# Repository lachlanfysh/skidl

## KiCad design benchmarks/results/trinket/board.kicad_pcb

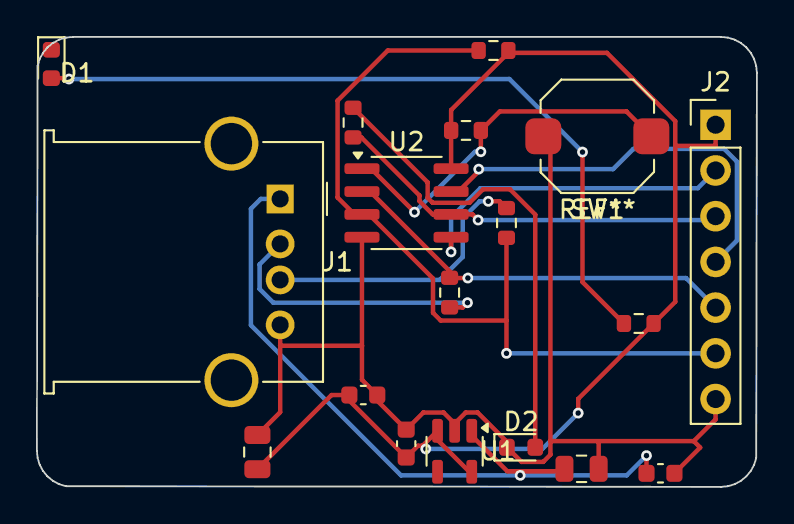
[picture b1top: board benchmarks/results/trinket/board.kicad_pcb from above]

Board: 2 copper layers, 40.0 x 25.0 mm, 18 parts (0 on the bottom side), 13 nets.

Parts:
C1, C3: 10uF; C_0805_2012Metric
C2, C4, C5: 100nF; C_0603_1608Metric
D1: GREEN; LED_0603_1608Metric
D2: RED; LED_0603_1608Metric
J1: USB_A; USB_A_Molex_67643_Horizontal
J2: GPIO; PinHeader_1x07_P2.54mm_Vertical
R1, R2: 68R; R_0603_1608Metric
R3: 1K5; R_0603_1608Metric
R4: 10K; R_0603_1608Metric
R5, R6: 1K; R_0603_1608Metric
SW1: RESET; SW_Push_1TS009xxxx-xxxx-xxxx_6x6x5mm
U1: MIC5205-3.3YM5; SOT-23-5
U2: ATtiny85; SOIC-8_3.9x4.9mm_P1.27mm

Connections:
3V3: C3.1, C4.1, C5.1, J2.1, R3.1, R4.1, R5.1, U1.3, U1.5, U2.8
GND: C1.2, C2.2, C3.2, C4.2, C5.2, D1.1, D2.1, J1.4, J2.7, SW1.2, U1.2, U2.4
unnamed: D1.2, R5.2
unnamed: D2.2, R6.2
PB0: J2.2, U2.5
PB1: J2.3, R6.1, U2.6
PB2: J2.4, U2.7
USB_DM: J2.5, R2.2, U2.2
USB_DM_RAW: J1.2, R2.1
USB_DP: J2.6, R1.2, R3.2, U2.3
USB_DP_RAW: J1.3, R1.1
VBUS: C1.1, C2.1, J1.1, U1.1
~RESET: R4.2, SW1.1, U2.1

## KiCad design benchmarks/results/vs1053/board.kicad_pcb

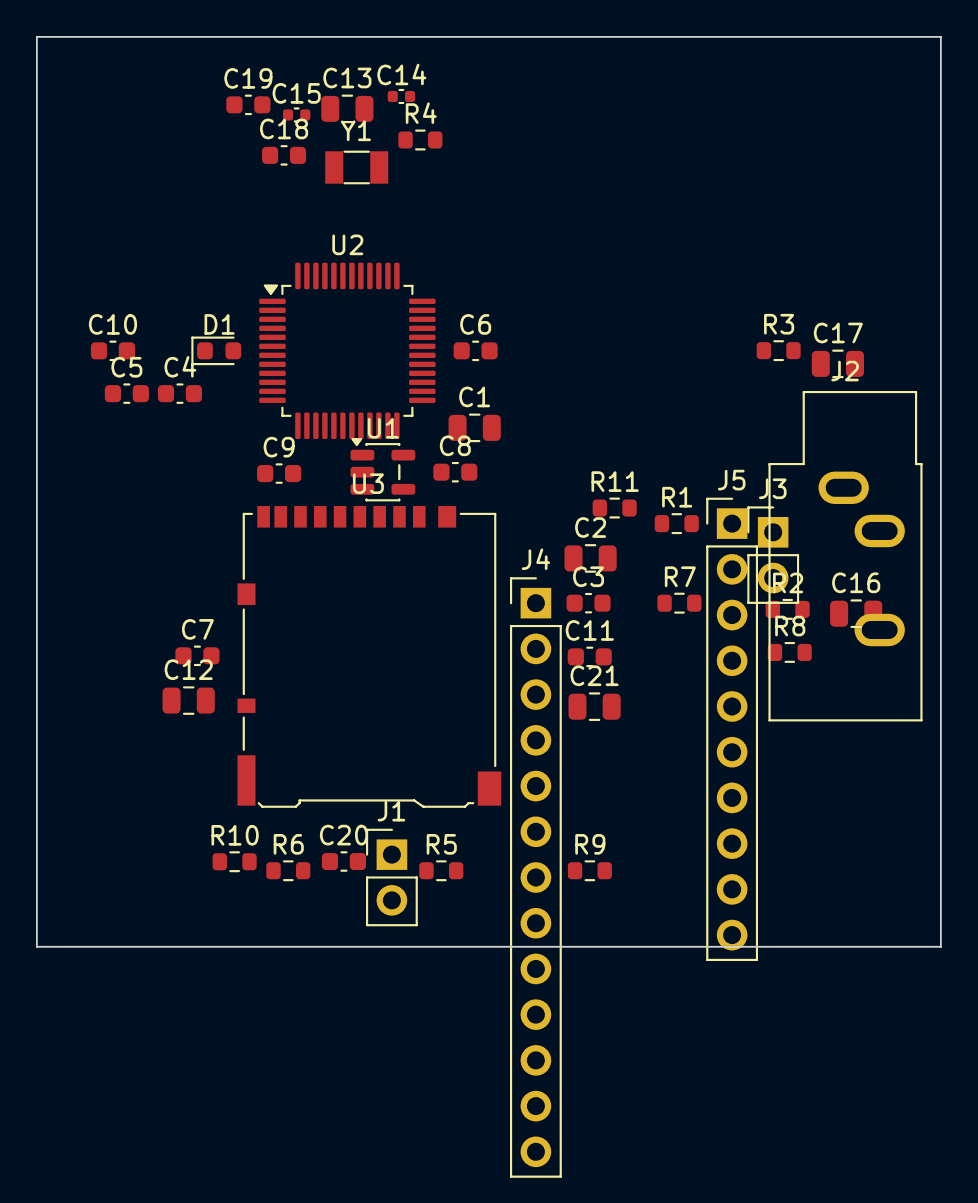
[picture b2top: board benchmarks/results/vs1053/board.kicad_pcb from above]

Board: 2 copper layers, 50.2 x 50.5 mm, 42 parts (0 on the bottom side), 38 nets, no tracks yet.

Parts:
C1, C2, C12, C13, C16, C17, C21: 10uF; C_0805_2012Metric
C3, C4, C5, C6, C7, C8, C9, C10, C11, C18, C19, C20: 100nF; C_0603_1608Metric
C14, C15: 15pF; C_0402_1005Metric
D1: GREEN; LED_0603_1608Metric
J1: PWR; PinHeader_1x02_P2.54mm_Vertical
J2: HP_JACK; Jack_3.5mm_CUI_SJ1-3533NG_Horizontal
J3: MIC; PinHeader_1x02_P2.54mm_Vertical
J4: SPI_HDR; PinHeader_1x13_P2.54mm_Vertical
J5: GPIO_HDR; PinHeader_1x10_P2.54mm_Vertical
R1: 1K; R_0603_1608Metric
R2, R3: 22; R_0603_1608Metric
R4: 2.2K; R_0603_1608Metric
R5, R6, R8, R9, R10: 10K; R_0603_1608Metric
R7: 100K; R_0603_1608Metric
R11: 220; R_0603_1608Metric
U1: AP2112K-3.3; SOT-23-5
U2: VS1053B; LQFP-48_7x7mm_P0.5mm
U3: MicroSD; microSD_HC_Hirose_DM3AT-SF-PEJM5
Y1: 12.288MHz; Crystal_SMD_3215-2Pin_3.2x1.5mm

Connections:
+1V8: C9.1, C10.1, C13.1, U2.5, U2.7, U2.21, U2.32, U2.42, U2.43
DREQ: J4.8, U2.8
GBUF: C5.1, U2.18
GND: C1.2, C2.2, C3.2, C4.2, C5.2, C6.2, C7.2, C8.2, C9.2, C10.2, C11.2, C12.2, C13.2, C14.2, C15.2, C19.2, C20.2, C21.2, J1.2, J2.S, J3.2, J4.2, J5.10, R1.2, U1.2, U2.15, U2.17, U2.31, U2.33, U2.38, U2.41, U2.44, U2.46, U3.6, U3.9
GPIO0: J5.1, U2.9
GPIO1: J5.2, U2.10
GPIO2: J5.3, U2.11
GPIO3: J5.4, U2.12
GPIO4: J5.5, U2.34
GPIO5: J5.6, U2.35
GPIO6: J5.7, U2.36
GPIO7: J5.8, U2.37
HP_L: C16.2, J2.T, R2.1
HP_R: C17.2, J2.R, R3.1
LINE_L: C16.1, U2.16
LINE_R: C17.1, U2.14
MIC_IN: C18.1, J3.1
MIC_N: C19.1, U2.2
MIC_P: C18.2, R4.2, U2.1
MIDI_RX: J5.9, R11.2, U2.23
MISO: J4.5, U2.27
MOSI: J4.4, U2.26
unnamed: D1.2, R1.1
unnamed: R5.2, U3.8
unnamed: R6.2, U3.1
RCAP: C4.1, U2.20
RESET_N: J4.9, R7.2, U2.30
SCI_CS: J4.6, R8.2, U2.28
SCK: J4.3, U2.25
SDI_CS: J4.7, R9.2, U2.40
SD_CS: J4.10, R10.2, U3.2
SD_MISO: J4.13, U3.7
SD_MOSI: J4.12, U3.3
SD_SCK: J4.11, U3.5
VCC: C2.1, C3.1, C6.1, C7.1, C8.1, C11.1, C12.1, C20.1, C21.1, D1.1, J4.1, R4.1, R5.1, R6.1, R7.1, R8.1, R9.1, R10.1, U1.5, U2.6, U2.13, U2.19, U2.22, U2.29, U2.39, U2.45, U3.4
VIN: C1.1, J1.1, U1.1, U1.3
XTAL_IN: C14.1, U2.3, Y1.1
XTAL_OUT: C15.1, U2.4, Y1.2

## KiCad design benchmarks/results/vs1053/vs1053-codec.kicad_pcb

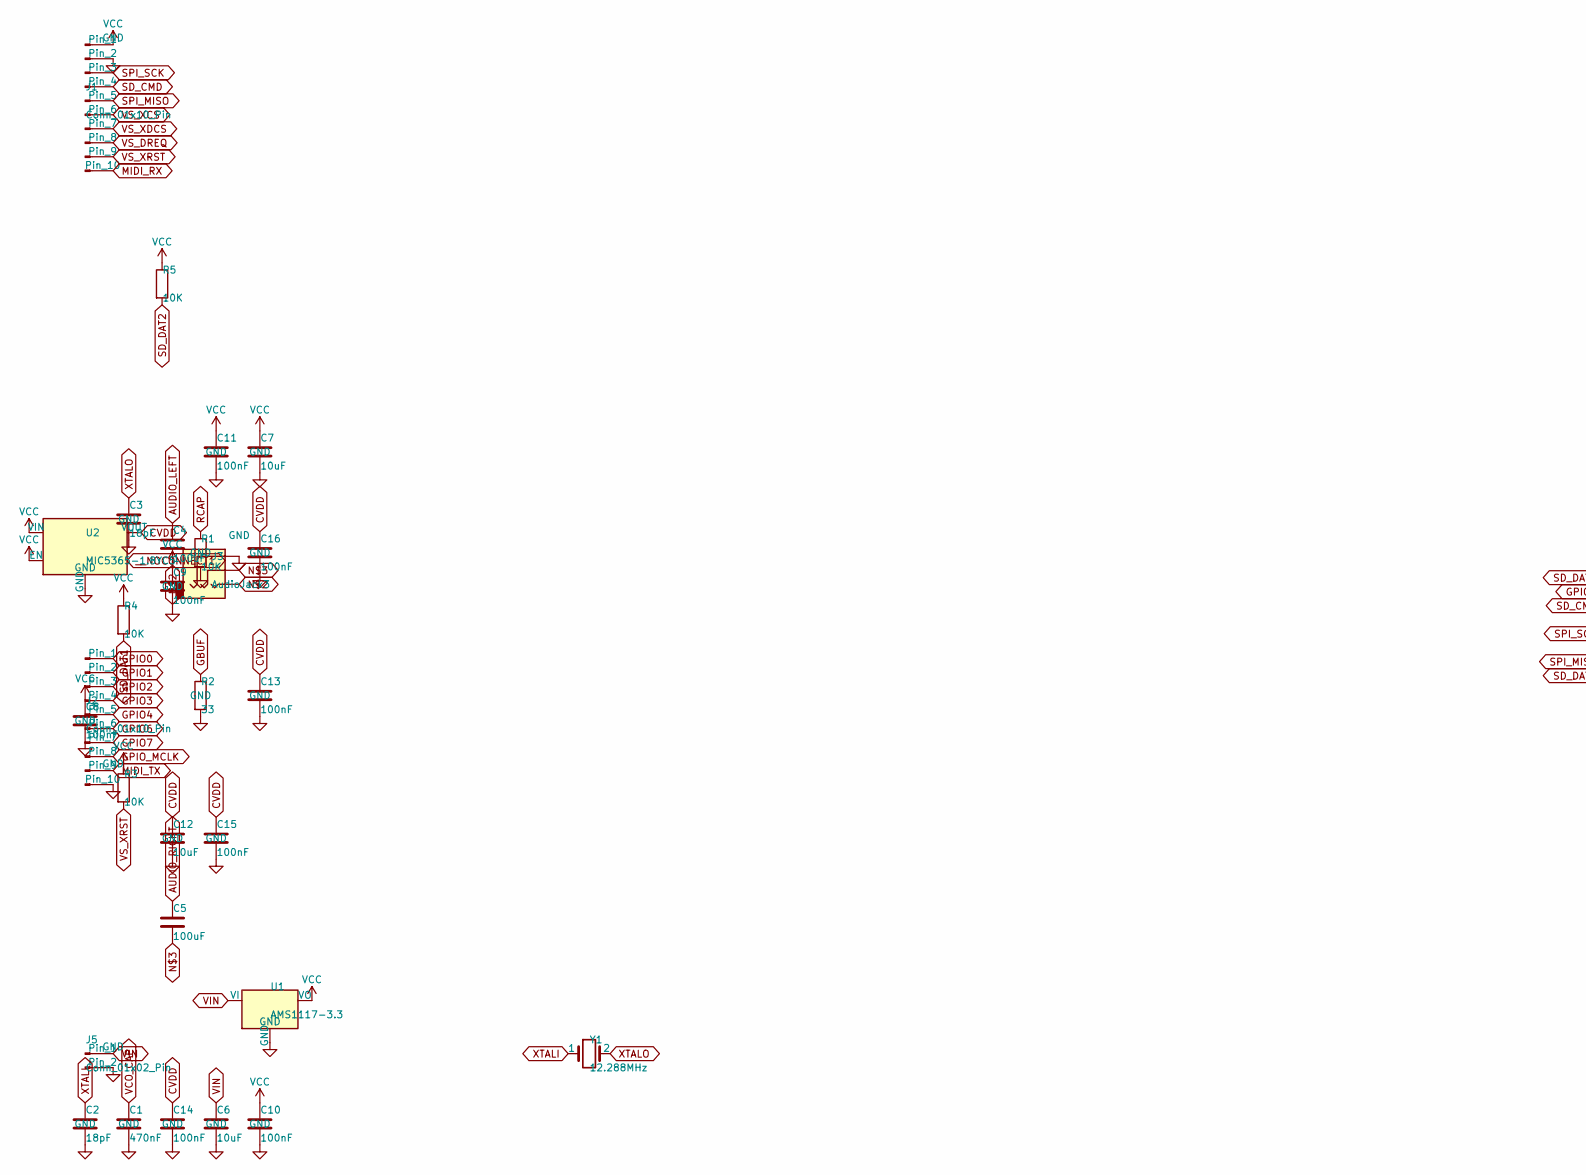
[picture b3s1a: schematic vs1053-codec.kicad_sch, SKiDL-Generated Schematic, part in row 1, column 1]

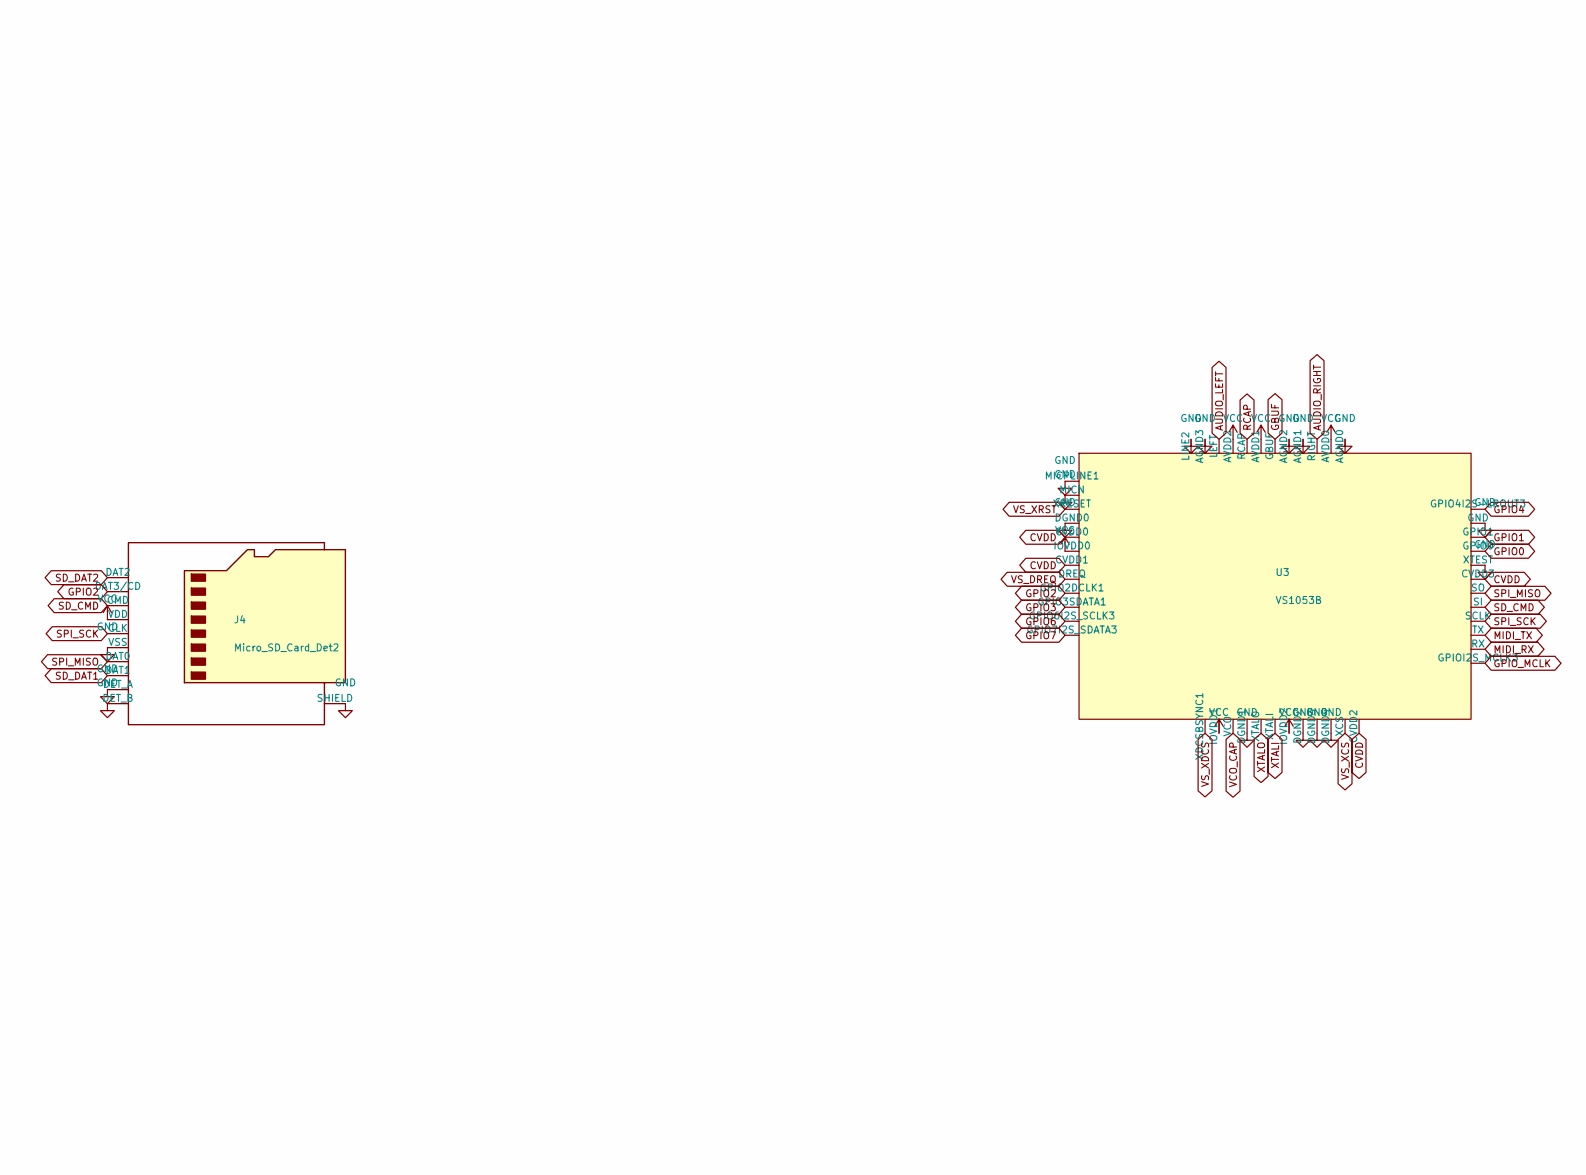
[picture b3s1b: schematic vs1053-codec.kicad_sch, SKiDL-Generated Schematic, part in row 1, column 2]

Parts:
C1: 470nF; C_0603_1608Metric
C2, C3: 18pF; C_0402_1005Metric
C4, C5: 100uF; C_1206_3216Metric
C6, C7, C12: 10uF; C_0805_2012Metric
C8, C9, C10, C11, C13, C14, C15, C16: 100nF; C_0603_1608Metric
J1, J2: Conn_01x10_Pin; PinHeader_1x10_P2.54mm_Vertical
J3: AudioJack3; Jack_3.5mm_CUI_SJ1-3513N_Horizontal
J4: Micro_SD_Card_Det2; microSD_HC_Hirose_DM3D-SF
J5: Conn_01x02_Pin; PinHeader_1x02_P2.54mm_Vertical
R1, R3, R4, R5: 10K; R_0603_1608Metric
R2: 33; R_0603_1608Metric
U1: AMS1117-3.3; SOT-223-3_TabPin2
U2: MIC5365-1.8YC5; SOT-353_SC-70-5
U3: VS1053B; LQFP-48_7x7mm_P0.5mm
Y1: 12.288MHz; Crystal_SMD_HC49-SD

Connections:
AUDIO_LEFT: C4.1, U3.46 (LEFT)
AUDIO_RIGHT: C5.1, U3.39 (RIGHT)
CVDD: C12.1, C13.1, C14.1, C15.1, C16.1, U2.5 (VOUT), U3.5 (CVDD0), U3.7 (CVDD1), U3.24 (CVDD2), U3.31 (CVDD3)
GBUF: R2.1, U3.42 (GBUF)
GND: C1.2, C2.2, C3.2, C6.2, C7.2, C8.2, C9.2, C10.2, C11.2, C12.2, C13.2, C14.2, C15.2, C16.2, J1.2, J2.10, J3.S, J4.6 (VSS), J4.9 (DET_B), J4.10 (DET_A), J4.11 (SHIELD), J5.2, R1.2, R2.2, U1.1 (GND), U2.2 (GND), U3.1 (MICPLINE1), U3.2 (MICN), U3.4 (DGND0), U3.16 (DGND1), U3.20 (DGND2), U3.21 (DGND3), U3.22 (DGND4), U3.32 (XTEST), U3.35 (GND), U3.37 (AGND0), U3.40 (AGND1), U3.41 (AGND2), U3.47 (AGND3), U3.48 (LINE2)
GPIO0: J2.1, U3.33 (GPIO0)
GPIO1: J2.2, U3.34 (GPIO1)
GPIO2: J2.3, J4.2 (DAT3/CD), U3.9 (GPIO2DCLK1)
GPIO3: J2.4, U3.10 (GPIO3SDATA1)
GPIO4: J2.5, U3.36 (GPIO4I2S-LROUT3)
GPIO6: J2.6, U3.11 (GPIO6I2S_SCLK3)
GPIO7: J2.7, U3.12 (GPIO7I2S_SDATA3)
GPIO_MCLK: J2.8, U3.25 (GPIOI2S_MCLK3)
MIDI_RX: J1.10, U3.26 (RX)
MIDI_TX: J2.9, U3.27 (TX)
unnamed: C5.2, J3.R
RCAP: R1.1, U3.44 (RCAP)
SD_CMD: J1.4, J4.3 (CMD), U3.29 (SI)
SD_DAT1: J4.8 (DAT1), R4.2
SD_DAT2: J4.1 (DAT2), R5.2
SPI_MISO: J1.5, J4.7 (DAT0), U3.30 (SO)
SPI_SCK: J1.3, J4.5 (CLK), U3.28 (SCLK)
VCO_CAP: C1.1, U3.15 (VCO)
VIN: C6.1, J5.1, U1.3 (VI)
VS_DREQ: J1.8, U3.8 (DREQ)
VS_XCS: J1.6, U3.23 (XCS)
VS_XDCS: J1.7, U3.13 (XDCSBSYNC1)
VS_XRST: J1.9, R3.2, U3.3 (XRESET)
XTALI: C2.1, U3.18 (XTALI), Y1.1
XTALO: C3.1, U3.17 (XTALO), Y1.2
__NOCONNECT1: U2.4 (NC)

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
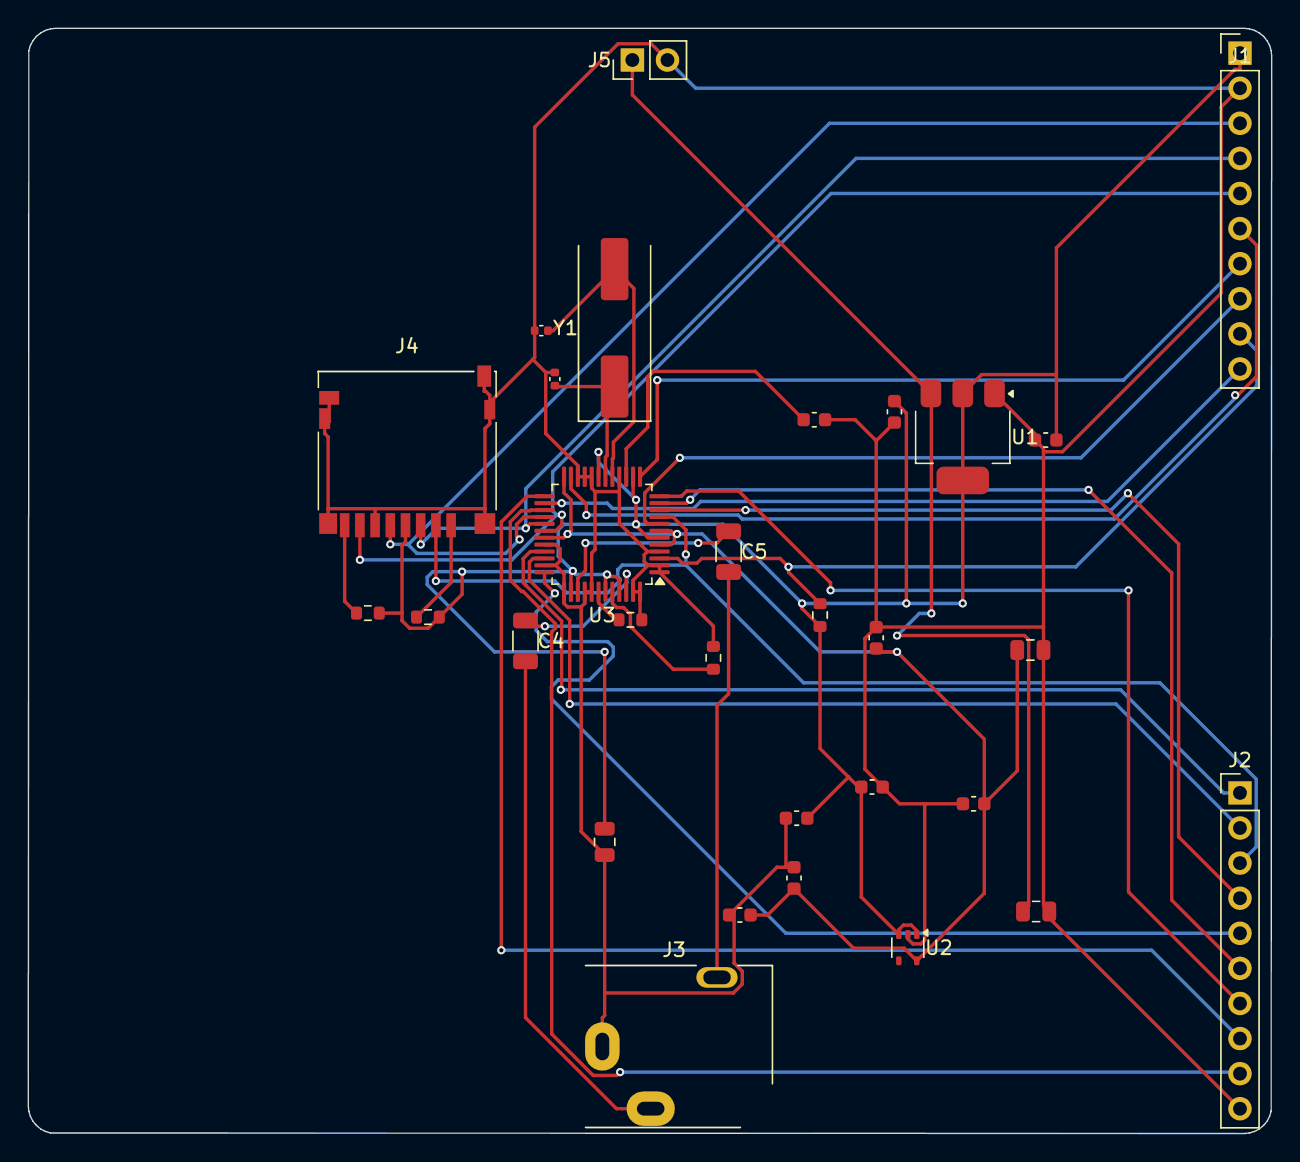
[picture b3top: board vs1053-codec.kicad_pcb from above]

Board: 2 copper layers, 90.0 x 80.0 mm, 30 parts (0 on the bottom side), 32 nets.

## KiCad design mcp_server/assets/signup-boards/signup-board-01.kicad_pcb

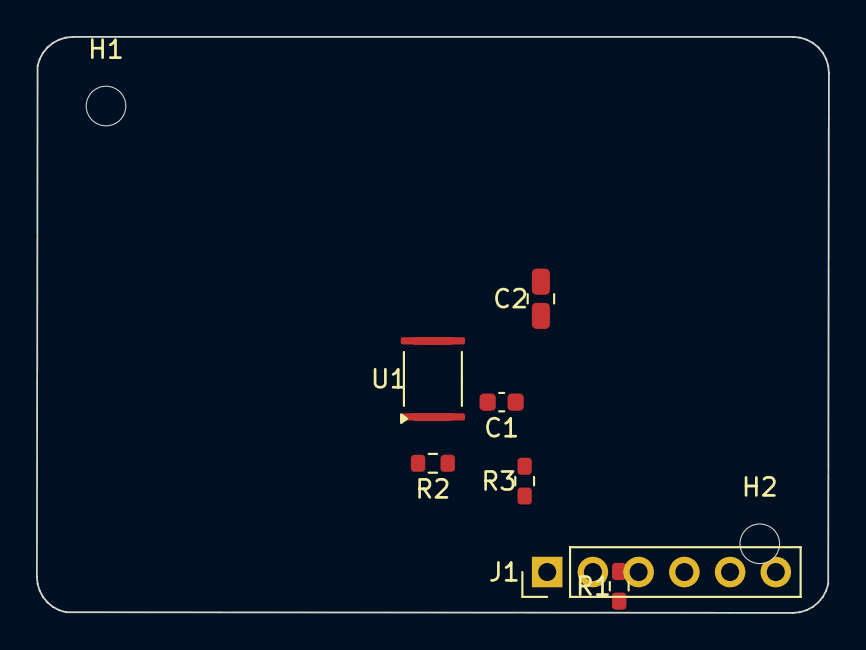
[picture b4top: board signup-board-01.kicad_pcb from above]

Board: 2 copper layers, 44.0 x 32.0 mm, 9 parts (0 on the bottom side), 5 nets, no tracks yet.

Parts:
C1: 100nF; C_0603_1608Metric
C2: 10uF; C_0805_2012Metric
H1, H2: MountingHole; MountingHole_2.2mm_M2
J1: Conn_01x06; PinHeader_1x06_P2.54mm_Vertical
R1, R2, R3: 10K; R_0603_1608Metric
U1: MCP9808_MSOP; MSOP-8_3x3mm_P0.65mm

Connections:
GND: C1.2, C2.2, J1.2, U1.4, U1.5, U1.6, U1.7
unnamed: J1.5, R3.2, U1.3
SCL: J1.4, R2.2, U1.2
SDA: J1.3, R1.2, U1.1
VDD: C1.1, C2.1, J1.1, R1.1, R2.1, R3.1, U1.8

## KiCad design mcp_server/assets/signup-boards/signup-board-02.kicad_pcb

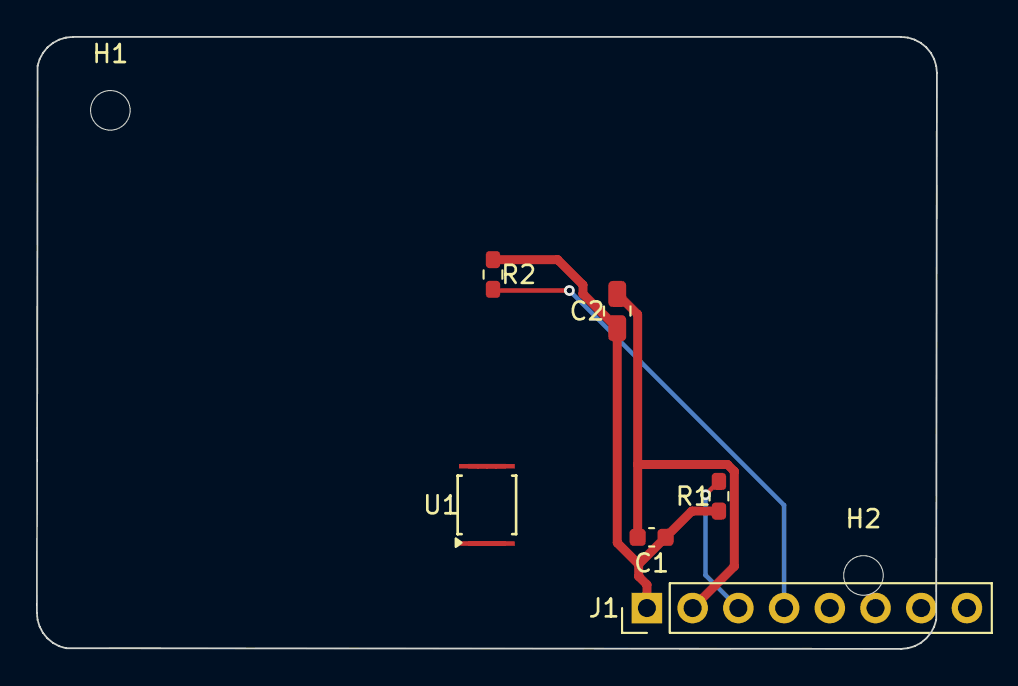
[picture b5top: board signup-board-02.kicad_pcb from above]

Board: 2 copper layers, 50.0 x 34.0 mm, 8 parts (0 on the bottom side), 8 nets.

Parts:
C1: 100nF; C_0603_1608Metric
C2: 10uF; C_0805_2012Metric
H1, H2: MountingHole; MountingHole_2.2mm_M2
J1: Conn_01x08; PinHeader_1x08_P2.54mm_Vertical
R1, R2: 10K; R_0603_1608Metric
U1: ADS1115IDGS; TSSOP-10_3x3mm_P0.5mm

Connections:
GND: C1.2, C2.2, J1.2, U1.1, U1.3
unnamed: J1.5, U1.4
unnamed: J1.6, U1.5
unnamed: J1.7, U1.6
unnamed: J1.8, U1.7
SCL: J1.4, R2.2, U1.10
SDA: J1.3, R1.2, U1.9
VDD: C1.1, C2.1, J1.1, R1.1, R2.1, U1.8

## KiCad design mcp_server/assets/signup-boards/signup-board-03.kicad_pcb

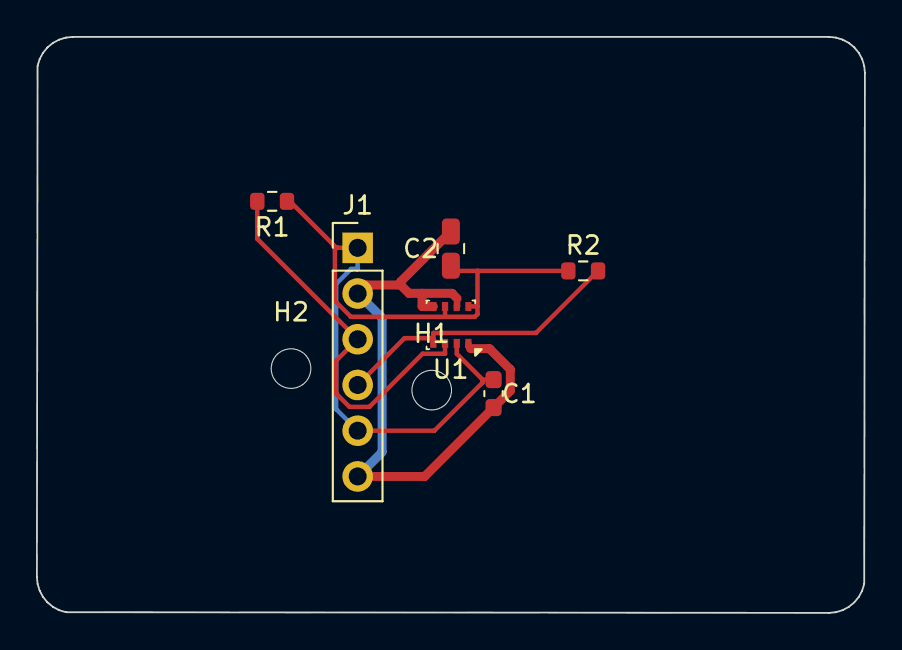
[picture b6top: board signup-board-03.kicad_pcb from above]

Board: 2 copper layers, 46.0 x 32.0 mm, 8 parts (0 on the bottom side), 4 nets.

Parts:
C1: 100nF; C_0603_1608Metric
C2: 10uF; C_0805_2012Metric
H1, H2: MountingHole; MountingHole_2.2mm_M2
J1: Conn_01x06; PinHeader_1x06_P2.54mm_Vertical
R1, R2: 10K; R_0603_1608Metric
U1: BME280; Bosch_LGA-8_2.5x2.5mm_P0.65mm_ClockwisePinNumbering

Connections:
3V3: C1.1, C2.1, J1.1, J1.5, R1.1, R2.1, U1.2, U1.6, U1.8
GND: C1.2, C2.2, J1.2, J1.6, U1.1, U1.5, U1.7
SCL: J1.4, R2.2, U1.4
SDA: J1.3, R1.2, U1.3

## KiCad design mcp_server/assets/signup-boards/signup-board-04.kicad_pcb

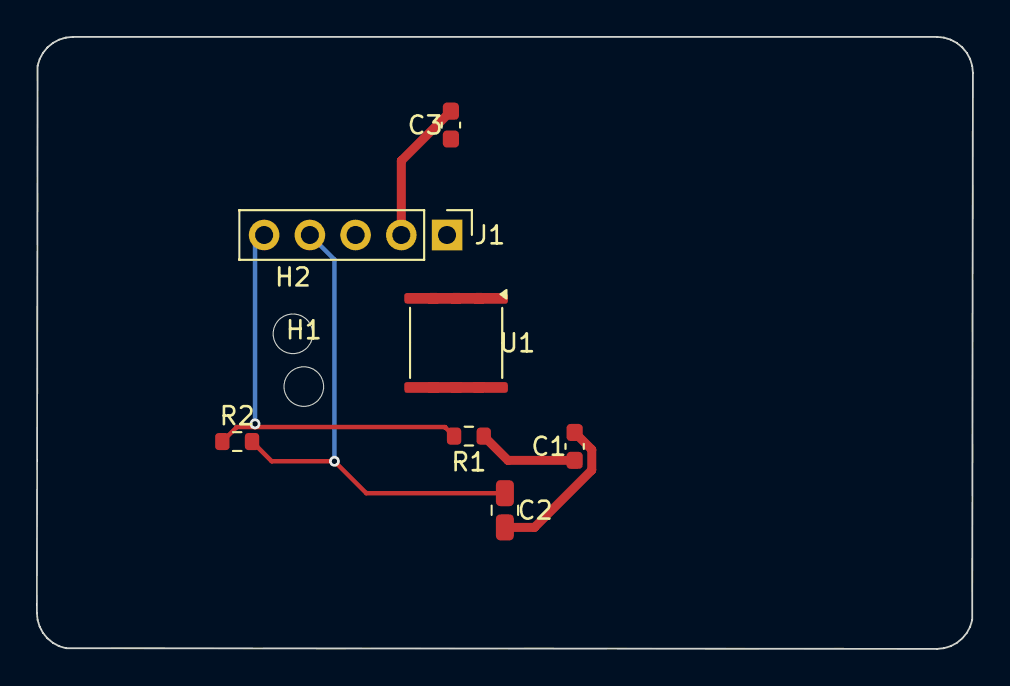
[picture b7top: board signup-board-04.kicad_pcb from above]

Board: 2 copper layers, 52.0 x 34.0 mm, 9 parts (0 on the bottom side), 6 nets.

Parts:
C1: 100nF; C_0603_1608Metric
C2: 10uF; C_0805_2012Metric
C3: 10nF; C_0603_1608Metric
H1, H2: MountingHole; MountingHole_2.2mm_M2
J1: Conn_01x05; PinHeader_1x05_P2.54mm_Vertical
R1: 10K; R_0603_1608Metric
R2: 100K; R_0603_1608Metric
U1: NE555D; SOIC-8_3.9x4.9mm_P1.27mm

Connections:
DISCH: J1.5, R1.2, R2.1, U1.7
GND: C1.2, C2.2, C3.2, J1.2, U1.1
unnamed: C3.1, U1.5
OUT: J1.3, U1.3
THRESH: C2.1, J1.4, R2.2, U1.2, U1.6
VCC: C1.1, J1.1, R1.1, U1.4, U1.8

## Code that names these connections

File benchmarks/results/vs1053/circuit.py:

from skidl import *

# Power rails
vin = Net("VIN"); vin.drive = POWER        # 5V input
vcc3v3 = Net("VCC"); vcc3v3.drive = POWER  # 3.3V digital/IO/analog rail
vcc1v8 = Net("CVDD"); vcc1v8.drive = POWER # 1.8V core rail for VS1053
gnd = Net("GND"); gnd.drive = POWER

# 3.3V LDO (AMS1117-3.3, SOT-223, 1A)
u_3v3 = Part("Regulator_Linear", "AMS1117-3.3",
             footprint="Package_TO_SOT_SMD:SOT-223-3_TabPin2")
vin += u_3v3["VI"]
gnd += u_3v3["GND"]
vcc3v3 += u_3v3["VO"]

# 1.8V LDO for VS1053 core (MIC5365-1.8YC5, SOT-353, 150mA)
u_1v8 = Part("Regulator_Linear", "MIC5365-1.8YC5",
             footprint="Package_TO_SOT_SMD:SOT-353_SC-70-5")
vcc3v3 += u_1v8["VIN"]
vcc3v3 += u_1v8["EN"]   # EN tied high = always on
gnd += u_1v8["GND"]
vcc1v8 += u_1v8["VOUT"]
u_1v8["NC"] += NC()

# VS1053B audio codec (EasyEDA/LCSC C9922, LQFP-48)
vs = Part("C9922", "VS1053B",
          footprint="Package_QFP:LQFP-48_7x7mm_P0.5mm")

# Core power (1.8V) — pins 5,7,24,31
vcc1v8 += vs["CVDD0"], vs["CVDD1"], vs["CVDD2"], vs["CVDD3"]
# IO power (3.3V) — pins 6,14,19
vcc3v3 += vs["IOVDD0"], vs["IOVDD1"], vs["IOVDD2"]
# Analog power (3.3V) — pins 38,43,45
vcc3v3 += vs["AVDD0"], vs["AVDD1"], vs["AVDD2"]
# Digital ground — pins 4,16,20,21,22,35
gnd += vs["DGND0"], vs["DGND1"], vs["DGND2"], vs["DGND3"], vs["DGND4"], vs["GND"]
# Analog ground — pins 37,40,41,47
gnd += vs["AGND0"], vs["AGND1"], vs["AGND2"], vs["AGND3"]

# XTEST: pull to GND for normal operation (pin 32)
gnd += vs["XTEST"]

# VCO filter cap (pin 15)
vco_net = Net("VCO_CAP")
vs["VCO"] += vco_net
c_vco = Part("Device", "C", value="470nF",
             footprint="Capacitor_SMD:C_0603_1608Metric")
vco_net += c_vco[1]
gnd += c_vco[2]

# RCAP: output resistance cap (pin 44) — 10K to GND
rcap_net = Net("RCAP")
vs["RCAP"] += rcap_net
r_rcap = Part("Device", "R", value="10K",
              footprint="Resistor_SMD:R_0603_1608Metric")
rcap_net += r_rcap[1]
gnd += r_rcap[2]

# GBUF: buffer output (pin 42) — 33 ohm to GND
gbuf_net = Net("GBUF")
vs["GBUF"] += gbuf_net
r_gbuf = Part("Device", "R", value="33",
              footprint="Resistor_SMD:R_0603_1608Metric")
gbuf_net += r_gbuf[1]
gnd += r_gbuf[2]

# 12.288 MHz crystal (pins 17=XTALO, 18=XTALI)
xtal = Part("Device", "Crystal",
            footprint="Crystal:Crystal_SMD_HC49-SD")
xtal.value = "12.288MHz"

xtali_net = Net("XTALI")
xtalo_net = Net("XTALO")
vs["XTALI"] += xtali_net
vs["XTALO"] += xtalo_net
xtal[1] += xtali_net
xtal[2] += xtalo_net

# Crystal load caps (18pF)
c_xi = Part("Device", "C", value="18pF",
            footprint="Capacitor_SMD:C_0402_1005Metric")
c_xo = Part("Device", "C", value="18pF",
            footprint="Capacitor_SMD:C_0402_1005Metric")
xtali_net += c_xi[1]; gnd += c_xi[2]
xtalo_net += c_xo[1]; gnd += c_xo[2]

# SPI interface signals
spi_sck  = Net("SPI_SCK")
spi_mosi = Net("SPI_MOSI")
spi_miso = Net("SPI_MISO")
vs_xcs   = Net("VS_XCS")    # VS1053 SPI control chip select (pin 23)
vs_xdcs  = Net("VS_XDCS")   # VS1053 SPI data chip select / BSYNC (pin 13)
vs_dreq  = Net("VS_DREQ")   # data request output (pin 8)
vs_xrst  = Net("VS_XRST")   # reset active-low (pin 3)
midi_rx  = Net("MIDI_RX")   # UART RX for MIDI (pin 26)
midi_tx  = Net("MIDI_TX")   # UART TX (pin 27)

vs["SCLK"] += spi_sck
vs["SI"]   += spi_mosi
vs["SO"]   += spi_miso
vs["XCS"]  += vs_xcs
vs["XDCSBSYNC1"] += vs_xdcs
vs["DREQ"] += vs_dreq
vs["XRESET"] += vs_xrst
vs["RX"]   += midi_rx
vs["TX"]   += midi_tx

# XRESET pull-up resistor
r_xrst = Part("Device", "R", value="10K",
              footprint="Resistor_SMD:R_0603_1608Metric")
vcc3v3 += r_xrst[1]
vs_xrst += r_xrst[2]

# GPIO signals (pins 33,34,9,10,36,11,12,25)
gpio0     = Net("GPIO0")
gpio1     = Net("GPIO1")
gpio2     = Net("GPIO2")
gpio3     = Net("GPIO3")
gpio4     = Net("GPIO4")
gpio6     = Net("GPIO6")
gpio7     = Net("GPIO7")
gpio_mclk = Net("GPIO_MCLK")

vs["GPIO0"]          += gpio0
vs["GPIO1"]          += gpio1
vs["GPIO2DCLK1"]     += gpio2
vs["GPIO3SDATA1"]    += gpio3
vs["GPIO4I2S-LROUT3"]  += gpio4
vs["GPIO6I2S_SCLK3"]   += gpio6
vs["GPIO7I2S_SDATA3"]  += gpio7
vs["GPIOI2S_MCLK3"]    += gpio_mclk

# MIC input pins — tie MICPLINE1 and LINE2 to AGND for breakout
gnd += vs["MICPLINE1"], vs["MICN"], vs["LINE2"]

# SPI header — 10 pin (3V3, GND, SCK, MOSI, MISO, XCS, XDCS, DREQ, XRST, MIDI_RX)
j_spi = Part("Connector", "Conn_01x10_Pin",
             footprint="Connector_PinHeader_2.54mm:PinHeader_1x10_P2.54mm_Vertical")
j_spi.edge_preference = "right"
vcc3v3  += j_spi["Pin_1"]
gnd     += j_spi["Pin_2"]
spi_sck  += j_spi["Pin_3"]
spi_mosi += j_spi["Pin_4"]
spi_miso += j_spi["Pin_5"]
vs_xcs   += j_spi["Pin_6"]
vs_xdcs  += j_spi["Pin_7"]
vs_dreq  += j_spi["Pin_8"]
vs_xrst  += j_spi["Pin_9"]
midi_rx  += j_spi["Pin_10"]

# GPIO header — 10 pin (GPIO0..7, MIDI_TX, GND)
j_gpio = Part("Connector", "Conn_01x10_Pin",
              footprint="Connector_PinHeader_2.54mm:PinHeader_1x10_P2.54mm_Vertical")
j_gpio.edge_preference = "right"
gpio0     += j_gpio["Pin_1"]
gpio1     += j_gpio["Pin_2"]
gpio2     += j_gpio["Pin_3"]
gpio3     += j_gpio["Pin_4"]
gpio4     += j_gpio["Pin_5"]
gpio6     += j_gpio["Pin_6"]
gpio7     += j_gpio["Pin_7"]
gpio_mclk += j_gpio["Pin_8"]
midi_tx  += j_gpio["Pin_9"]
gnd      += j_gpio["Pin_10"]

# 3.5mm stereo headphone jack
# CUI SJ1-3513N footprint uses pad names T/R/S — matches AudioJack3 symbol pin numbers
j_hp = Part("Connector_Audio", "AudioJack3",
            footprint="Connector_Audio:Jack_3.5mm_CUI_SJ1-3513N_Horizontal")
j_hp.edge_preference = "bottom"

# Line output coupling caps (100uF — SMD 1206)
audio_left_raw  = Net("AUDIO_LEFT")
audio_right_raw = Net("AUDIO_RIGHT")
vs["LEFT"]  += audio_left_raw
vs["RIGHT"] += audio_right_raw

c_left = Part("Device", "C", value="100uF",
              footprint="Capacitor_SMD:C_1206_3216Metric")
c_right = Part("Device", "C", value="100uF",
               footprint="Capacitor_SMD:C_1206_3216Metric")
audio_left_raw  += c_left[1];  c_left[2]  += j_hp["T"]   # Tip = Left
audio_right_raw += c_right[1]; c_right[2] += j_hp["R"]   # Ring = Right
gnd += j_hp["S"]                                           # Sleeve = GND

# MicroSD socket (SPI mode) — Hirose DM3D-SF has 11 pads; use Micro_SD_Card_Det2 (11 pins)
sd = Part("Connector", "Micro_SD_Card_Det2",
          footprint="Connector_Card:microSD_HC_Hirose_DM3D-SF")

sd_clk  = Net("SD_CLK")
sd_cmd  = Net("SD_CMD")   # MOSI in SPI mode
sd_dat0 = Net("SD_DAT0")  # MISO in SPI mode
sd_cs   = Net("SD_CS")    # CS (DAT3/CD in SPI mode)
sd_dat1 = Net("SD_DAT1")
sd_dat2 = Net("SD_DAT2")

vcc3v3 += sd["VDD"]
gnd    += sd["VSS"]
gnd    += sd["SHIELD"]
# Card detect pins: DET_A and DET_B are normally-closed switch; tie both to GND
gnd    += sd["DET_A"]
gnd    += sd["DET_B"]

# SD shares the SPI bus with VS1053
spi_sck  += sd_clk;  sd["CLK"]     += sd_clk
spi_mosi += sd_cmd;  sd["CMD"]     += sd_cmd
spi_miso += sd_dat0; sd["DAT0"]    += sd_dat0
sd_cs    += sd["DAT3/CD"]

# SD unused data lines pulled high
sd["DAT1"] += sd_dat1
sd["DAT2"] += sd_dat2
r_sd1 = Part("Device", "R", value="10K", footprint="Resistor_SMD:R_0603_1608Metric")
r_sd2 = Part("Device", "R", value="10K", footprint="Resistor_SMD:R_0603_1608Metric")
vcc3v3 += r_sd1[1]; sd_dat1 += r_sd1[2]
vcc3v3 += r_sd2[1]; sd_dat2 += r_sd2[2]

# SD CS on its own GPIO2 line (or bring out on separate header pin)
gpio2 += sd_cs

# 5V input power connector
j_pwr = Part("Connector", "Conn_01x02_Pin",
             footprint="Connector_PinHeader_2.54mm:PinHeader_1x02_P2.54mm_Vertical")
j_pwr.edge_preference = "top"
vin += j_pwr["Pin_1"]
gnd += j_pwr["Pin_2"]

# --- Decoupling caps ---

# VIN 10uF bulk
c_vin = Part("Device", "C", value="10uF", footprint="Capacitor_SMD:C_0805_2012Metric")
vin += c_vin[1]; gnd += c_vin[2]

# 3.3V rail: 10uF bulk + 100nF x4
c_3v3_b = Part("Device", "C", value="10uF", footprint="Capacitor_SMD:C_0805_2012Metric")
vcc3v3 += c_3v3_b[1]; gnd += c_3v3_b[2]
for _ in range(4):
    c = Part("Device", "C", value="100nF", footprint="Capacitor_SMD:C_0603_1608Metric")
    vcc3v3 += c[1]; gnd += c[2]

# 1.8V CVDD rail: 10uF bulk + 100nF x4
c_1v8_b = Part("Device", "C", value="10uF", footprint="Capacitor_SMD:C_0805_2012Metric")
vcc1v8 += c_1v8_b[1]; gnd += c_1v8_b[2]
for _ in range(4):
    c = Part("Device", "C", value="100nF", footprint="Capacitor_SMD:C_0603_1608Metric")
    vcc1v8 += c[1]; gnd += c[2]

# Larger board outline to reduce congestion on dense LQFP-48
EDA_FLOORPLAN = {
    "outline": {"width_mm": 90, "height_mm": 80, "corner_radius_mm": 2},
    "edge_anchors": [
        {"ref": "J3", "edge": "bottom"},
        {"ref": "J5", "edge": "top"},
    ],
}

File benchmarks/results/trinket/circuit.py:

"""
Trinket ATtiny85 dev board — SKiDL circuit description.

Based on the Adafruit Trinket hardware:
- ATtiny85-20S (SOIC-8) MCU with V-USB software USB
- USB-A male plug (horizontal, plugs directly into host USB port)
- MIC5225-3.3YM5 SOT-23-5 3.3V LDO regulator
- Green power LED (always on)
- Red user LED on PB1 (Arduino digital pin 1)
- Tactile reset button
- 5 GPIO pins broken out on 0.1" header
- Board ~31x15mm

V-USB wiring (low-speed, per Adafruit Trinket reference design):
  D- → PB3/XTAL1 (pin 2) via 68R
  D+ → PB4/XTAL2 (pin 3) via 68R + 1.5kΩ pull-up to 3.3V

LCSC converted parts:
  MIC5225-3.3YM5-TR: C512101
"""

from skidl import *

set_default_tool(KICAD9)

# ---------------------------------------------------------------------------
# Power rails
# ---------------------------------------------------------------------------
vbus = Net("VBUS"); vbus.drive = POWER    # 5V from USB host
vcc = Net("3V3"); vcc.drive = POWER       # 3.3V regulated
gnd = Net("GND"); gnd.drive = POWER

# ---------------------------------------------------------------------------
# Signal nets
# ---------------------------------------------------------------------------
usb_dp_raw = Net("USB_DP_RAW")   # D+ at connector
usb_dm_raw = Net("USB_DM_RAW")   # D- at connector
usb_dp = Net("USB_DP")           # D+ at MCU (post 68R)
usb_dm = Net("USB_DM")           # D- at MCU (post 68R)
reset_n = Net("~{RESET}")
pb0 = Net("PB0")
pb1 = Net("PB1")                  # Red LED / Arduino pin 1
pb2 = Net("PB2")

# ---------------------------------------------------------------------------
# USB-A male plug (horizontal, board plugs into host port)
# ---------------------------------------------------------------------------
@subcircuit
def usb_connector(vbus, gnd, dp_raw, dm_raw):
    usb = Part("Connector", "USB_A",
               footprint="Connector_USB:USB_A_Molex_67643_Horizontal")
    usb.edge_preference = "left"
    vbus += usb["VBUS"]
    gnd  += usb["GND"]
    dp_raw += usb["D+"]
    dm_raw += usb["D-"]

usb_connector(vbus, gnd, usb_dp_raw, usb_dm_raw)

# ---------------------------------------------------------------------------
# 3.3V LDO: MIC5205-3.3YM5 (SOT-23-5, KiCad symbol — functional equiv of MIC5225)
# Pins: IN=1, GND=2, EN=3, BP=4, OUT=5
# EN tied high = always on. BP = bypass cap pin (float/NC on MIC5225 equivalent)
# ---------------------------------------------------------------------------
@subcircuit
def power_block(vin, vout, gnd):
    reg = Part("Regulator_Linear", "MIC5205-3.3YM5",
               footprint="Package_TO_SOT_SMD:SOT-23-5")
    vin  += reg["IN"]
    gnd  += reg["GND"]
    vout += reg["OUT"]
    vout += reg["EN"]   # EN tied high = always on
    reg["BP"] += NC     # Bypass cap pin (optional noise filter, left open)

    # Input bulk + decoupling
    c_in = Part("Device", "C_Polarized", value="10uF",
                footprint="Capacitor_SMD:C_0805_2012Metric")
    vin += c_in[1]; gnd += c_in[2]

    c_in_dec = Part("Device", "C", value="100nF",
                    footprint="Capacitor_SMD:C_0603_1608Metric")
    vin += c_in_dec[1]; gnd += c_in_dec[2]

    # Output bulk + decoupling
    c_out = Part("Device", "C_Polarized", value="10uF",
                 footprint="Capacitor_SMD:C_0805_2012Metric")
    vout += c_out[1]; gnd += c_out[2]

    c_out_dec = Part("Device", "C", value="100nF",
                     footprint="Capacitor_SMD:C_0603_1608Metric")
    vout += c_out_dec[1]; gnd += c_out_dec[2]

power_block(vbus, vcc, gnd)

# ---------------------------------------------------------------------------
# V-USB data lines: 68R series + 1.5k D+ pull-up
# ---------------------------------------------------------------------------
@subcircuit
def vusb_data(dp_raw, dm_raw, dp_mcu, dm_mcu, vcc):
    r_dp = Part("Device", "R", value="68R",
                footprint="Resistor_SMD:R_0603_1608Metric")
    dp_raw += r_dp[1]; dp_mcu += r_dp[2]

    r_dm = Part("Device", "R", value="68R",
                footprint="Resistor_SMD:R_0603_1608Metric")
    dm_raw += r_dm[1]; dm_mcu += r_dm[2]

    # 1.5kΩ pull-up on D+ for low-speed USB device signalling
    r_pu = Part("Device", "R", value="1K5",
                footprint="Resistor_SMD:R_0603_1608Metric")
    vcc += r_pu[1]; dp_mcu += r_pu[2]

vusb_data(usb_dp_raw, usb_dm_raw, usb_dp, usb_dm, vcc)

# ---------------------------------------------------------------------------
# ATtiny85-20S (SOIC-8) MCU
# V-USB: D-=PB3/XTAL1, D+=PB4/XTAL2 (per Adafruit Trinket schematic)
# ---------------------------------------------------------------------------
@subcircuit
def mcu_block(vcc, gnd, reset_n, pb0, pb1, pb2, usb_dp, usb_dm):
    mcu = Part("MCU_Microchip_ATtiny", "ATtiny85-20S",
               footprint="Package_SO:SOIC-8_3.9x4.9mm_P1.27mm",
               value="ATtiny85")
    mcu["VCC"] += vcc
    mcu["GND"] += gnd
    mcu["~{RESET}/PB5"] += reset_n
    mcu["AREF/PB0"] += pb0
    mcu["PB1"] += pb1
    mcu["PB2"] += pb2
    mcu["XTAL1/PB3"] += usb_dm   # D-
    mcu["XTAL2/PB4"] += usb_dp   # D+

    # MCU VCC decoupling
    c_dec = Part("Device", "C", value="100nF",
                 footprint="Capacitor_SMD:C_0603_1608Metric")
    vcc += c_dec[1]; gnd += c_dec[2]

    # Reset pull-up + button
    r_rst = Part("Device", "R", value="10K",
                 footprint="Resistor_SMD:R_0603_1608Metric")
    vcc += r_rst[1]; reset_n += r_rst[2]

    sw_rst = Part("Switch", "SW_Push",
                  footprint="Button_Switch_SMD:SW_Push_1TS009xxxx-xxxx-xxxx_6x6x5mm",
                  value="RESET")
    reset_n += sw_rst[1]; gnd += sw_rst[2]

mcu_block(vcc, gnd, reset_n, pb0, pb1, pb2, usb_dp, usb_dm)

# ---------------------------------------------------------------------------
# LEDs: green power + red user (PB1)
# ---------------------------------------------------------------------------
@subcircuit
def led_block(vcc, gnd, pb1):
    # Green power LED (anode = pin 2, cathode = pin 1 per KiCad LED symbol)
    led_pwr = Part("Device", "LED", value="GREEN",
                   footprint="LED_SMD:LED_0603_1608Metric")
    r_pwr = Part("Device", "R", value="1K",
                 footprint="Resistor_SMD:R_0603_1608Metric")
    vcc += r_pwr[1]; r_pwr[2] += led_pwr["A"]
    gnd += led_pwr["K"]

    # Red user LED on PB1
    led_usr = Part("Device", "LED", value="RED",
                   footprint="LED_SMD:LED_0603_1608Metric")
    r_usr = Part("Device", "R", value="1K",
                 footprint="Resistor_SMD:R_0603_1608Metric")
    pb1 += r_usr[1]; r_usr[2] += led_usr["A"]
    gnd += led_usr["K"]

led_block(vcc, gnd, pb1)

# ---------------------------------------------------------------------------
# GPIO header: PB0, PB1, PB2, PB3(D-), PB4(D+), 3V3, GND
# 7-pin 0.1" header on board edge
# ---------------------------------------------------------------------------
@subcircuit
def gpio_header(vcc, gnd, pb0, pb1, pb2, usb_dm, usb_dp):
    hdr = Part("Connector_Generic", "Conn_01x07",
               footprint="Connector_PinHeader_2.54mm:PinHeader_1x07_P2.54mm_Vertical",
               value="GPIO")
    hdr.edge_preference = "right"
    hdr[1] += vcc
    hdr[2] += pb0
    hdr[3] += pb1
    hdr[4] += pb2
    hdr[5] += usb_dm   # PB3
    hdr[6] += usb_dp   # PB4
    hdr[7] += gnd

gpio_header(vcc, gnd, pb0, pb1, pb2, usb_dm, usb_dp)

# ---------------------------------------------------------------------------
# Board floorplan: 40x25mm (compact but routable dev board)
# USB-A plug hangs off left edge (edge connector). GPIO header at right.
# ---------------------------------------------------------------------------
EDA_FLOORPLAN = {
    "outline": {"width_mm": 40, "height_mm": 25, "corner_radius_mm": 1.5},
}
